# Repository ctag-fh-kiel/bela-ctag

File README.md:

## Resources regarding [CTAG-audio](http://ctag-audio.de/) capes for BeagleBone single board computers.

See [Wiki](https://github.com/ctag-fh-kiel/bela-ctag/wiki) for getting started with native Linux applications and CTAG multi-audio boards.

*CTAG multi-audio IO capes are compatible with the ultra-low-latency [Bela platform](http://bela.io/) and are available via [Bela's online shop](https://shop.bela.io/ctag).*

## Open source hardware resources include: 
- Schematic in pdf 
- Kicad 4.0.7 project data (PCB does not contain routed copper layers at this point --> will be added after some time together with BOM etc.)
- Licensed under [cc-by-nc-sa-4.0](https://creativecommons.org/licenses/by-nc-sa/4.0)

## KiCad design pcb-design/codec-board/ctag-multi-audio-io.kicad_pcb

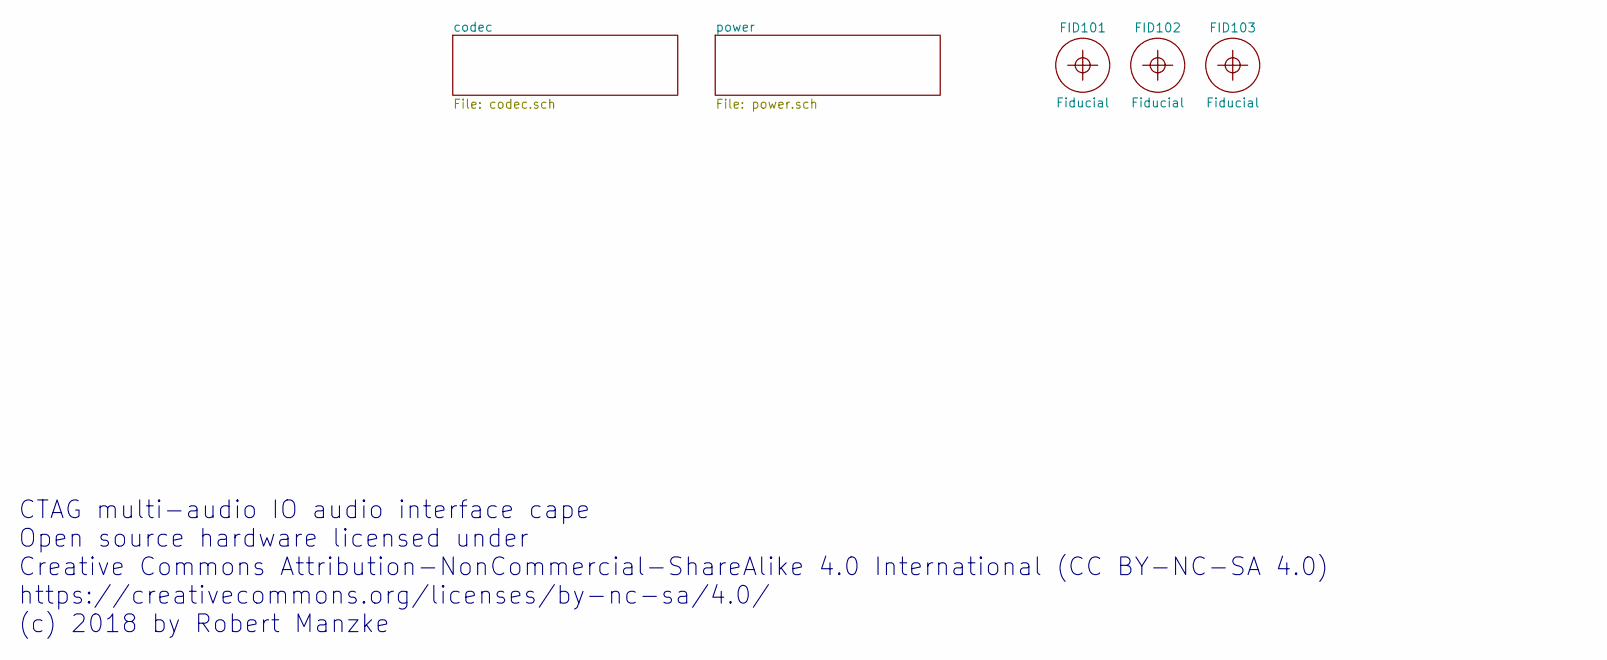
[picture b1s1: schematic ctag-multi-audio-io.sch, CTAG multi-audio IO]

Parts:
FID101, FID102, FID103: Fiducial; Fiducial_1mm_Dia_2.54mm_Outer_CopperTop

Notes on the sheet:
CTAG multi-audio IO audio interface cape Open source hardware licensed under Creative Commons Attribution-NonCommercial-ShareAlike 4.0 International (CC BY-NC-SA 4.0) https://creativecommons.org/licenses/by-nc-sa/4.0/ (c) 2018 by Robert Manzke

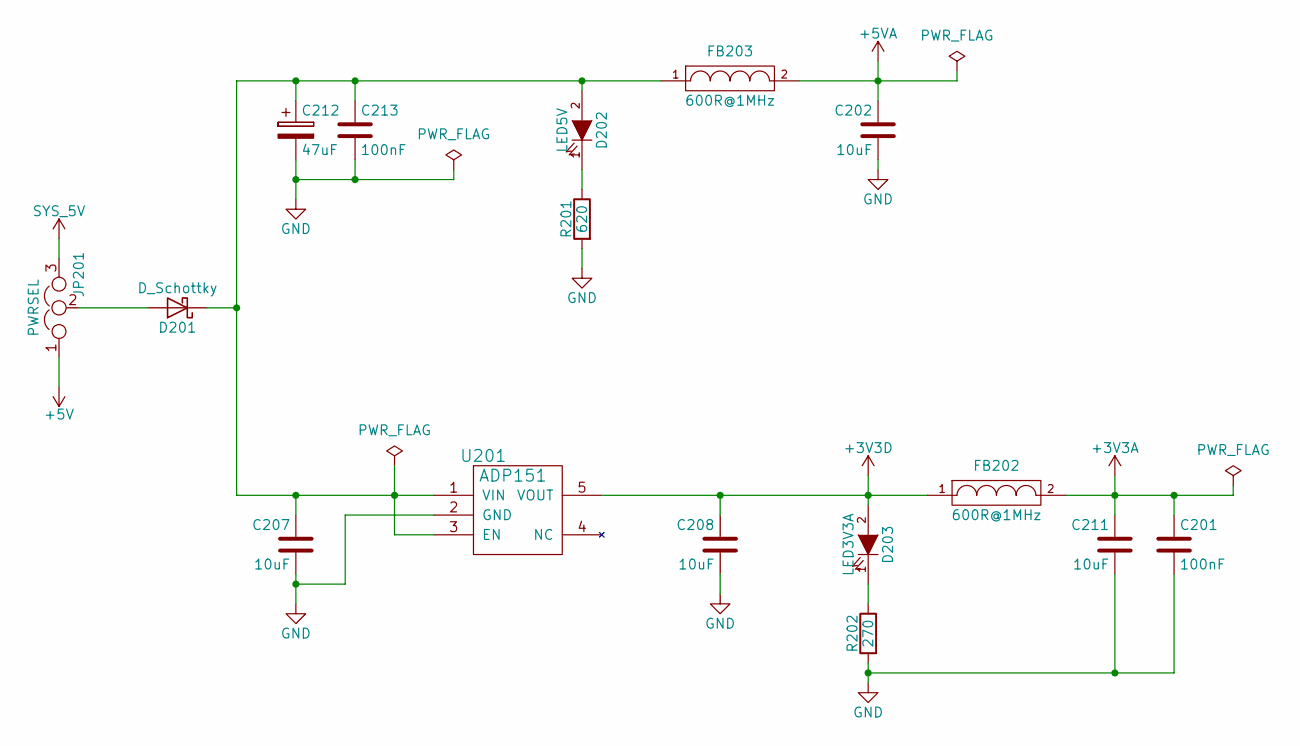
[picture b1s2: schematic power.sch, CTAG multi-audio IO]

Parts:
C201, C213: 100nF; C_0603
C202, C207, C208, C211: 10uF; C_0805
C212: 47uF; TantalC_SizeA_EIA-3216_Reflow
D201: D_Schottky; SOD-123
D202: LED5V; LED-0603
D203: LED3V3A; LED-0603
FB202, FB203: 600R@1MHz; C_0805
JP201: PWRSEL; Pin_Header_Straight_1x03
R201: 620; C_0603
R202: 270; C_0603
U201: ADP151; TSOT-23-5

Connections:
+3V3A: C201.1, C211.1, FB202.2; also elsewhere on the board
+3V3D: C208.1, D203.2 (A), FB202.1, U201.5 (VOUT); also elsewhere on the board
+5V: JP201.1; also elsewhere on the board
+5VA: C202.1, FB203.2; also elsewhere on the board
GND: C201.2, C202.2, C207.2, C208.2, C211.2, C212.2, C213.2, R201.2, R202.2, U201.2 (GND); also elsewhere on the board
unnamed: C207.1, C212.1, C213.1, D201.1 (K), D202.2 (A), FB203.1, U201.1 (VIN), U201.3 (EN)
unnamed: D201.2 (A), JP201.2
unnamed: D202.1 (K), R201.1
unnamed: D203.1 (K), R202.1
SYS_5V: JP201.3; also elsewhere on the board

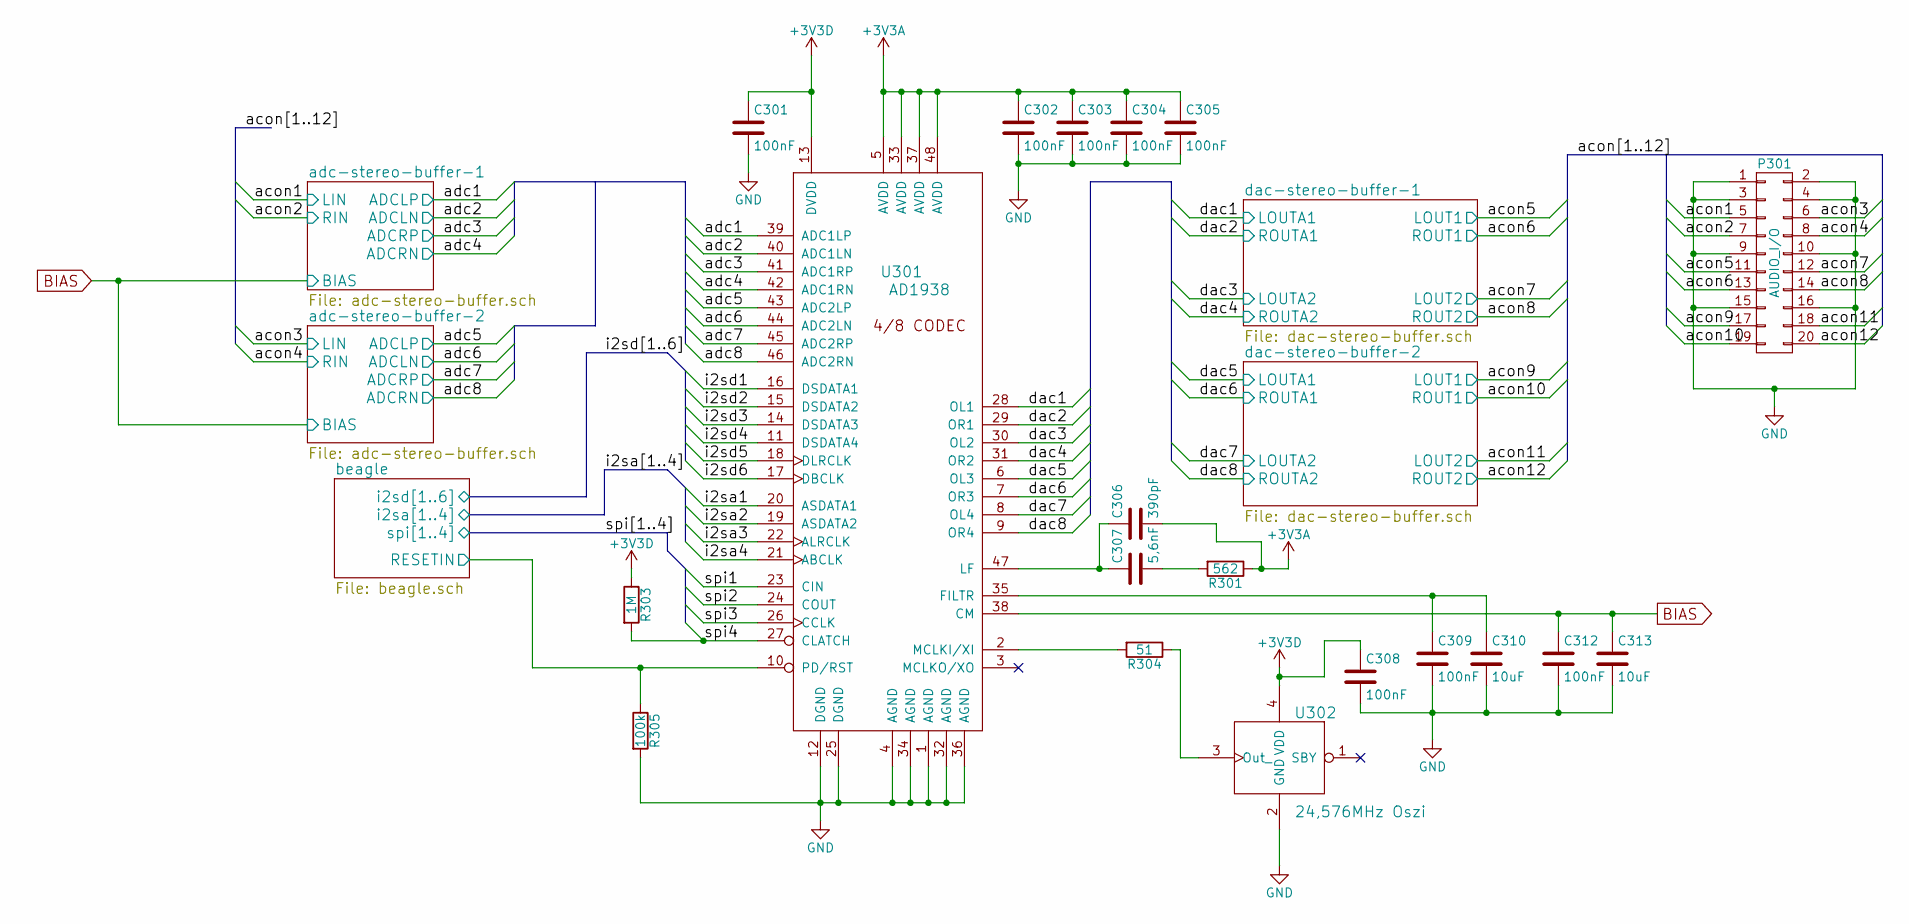
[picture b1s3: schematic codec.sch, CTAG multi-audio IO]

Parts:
C301, C302, C303, C304, C305, C308, C309, C312: 100nF; C_0603
C306: 390pF; C_0603
C307: 5,6nF; C_0603
C310, C313: 10uF; C_0805
P301: AUDIO_I/O; Pin_Header_Angled_2x10
R301: 562; C_0603
R303: 1M; C_0603
R304: 51; C_0603
R305: 100k; C_0603
U301: AD1938; LQFP-48_7x7mm_Pitch0.5mm
U302: 24,576MHz Oszi; Oszi_3.2x2.5mm

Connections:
+3V3A: C302.1, C303.1, C304.1, C305.1, C306.2, R301.1, U301.5 (AVDD), U301.33 (AVDD), U301.37 (AVDD), U301.48 (AVDD); also elsewhere on the board
+3V3D: C301.1, C308.1, R303.1, U301.13 (DVDD), U302.4 (VDD); also elsewhere on the board
/codec/acon1: P301.5; also elsewhere on the board
/codec/acon2: P301.7; also elsewhere on the board
/codec/acon3: P301.6; also elsewhere on the board
/codec/acon4: P301.8; also elsewhere on the board
/codec/acon5: P301.11; also elsewhere on the board
/codec/acon6: P301.13; also elsewhere on the board
/codec/acon7: P301.12; also elsewhere on the board
/codec/acon8: P301.14; also elsewhere on the board
/codec/acon9: P301.17; also elsewhere on the board
/codec/acon10: P301.19; also elsewhere on the board
/codec/acon11: P301.18; also elsewhere on the board
/codec/acon12: P301.20; also elsewhere on the board
/codec/adc1: U301.39 (ADC1LP); also elsewhere on the board
/codec/adc2: U301.40 (ADC1LN); also elsewhere on the board
/codec/adc3: U301.41 (ADC1RP); also elsewhere on the board
/codec/adc4: U301.42 (ADC1RN); also elsewhere on the board
/codec/adc5: U301.43 (ADC2LP); also elsewhere on the board
/codec/adc6: U301.44 (ADC2LN); also elsewhere on the board
/codec/adc7: U301.45 (ADC2RP); also elsewhere on the board
/codec/adc8: U301.46 (ADC2RN); also elsewhere on the board
/codec/beagle/RESETIN: R305.1, U301.10 (PD/RST); also elsewhere on the board
/codec/dac1: U301.28 (OL1); also elsewhere on the board
/codec/dac2: U301.29 (OR1); also elsewhere on the board
/codec/dac3: U301.30 (OL2); also elsewhere on the board
/codec/dac4: U301.31 (OR2); also elsewhere on the board
/codec/dac5: U301.6 (OL3); also elsewhere on the board
/codec/dac6: U301.7 (OR3); also elsewhere on the board
/codec/dac7: U301.8 (OL4); also elsewhere on the board
/codec/dac8: U301.9 (OR4); also elsewhere on the board
/codec/i2sa1: U301.20 (ASDATA1); also elsewhere on the board
/codec/i2sa2: U301.19 (ASDATA2); also elsewhere on the board
/codec/i2sa3: U301.22 (ALRCLK); also elsewhere on the board
/codec/i2sa4: U301.21 (ABCLK); also elsewhere on the board
/codec/i2sd1: U301.16 (DSDATA1); also elsewhere on the board
/codec/i2sd2: U301.15 (DSDATA2); also elsewhere on the board
/codec/i2sd3: U301.14 (DSDATA3)
/codec/i2sd4: U301.11 (DSDATA4)
/codec/i2sd5: U301.18 (DLRCLK); also elsewhere on the board
/codec/i2sd6: U301.17 (DBCLK); also elsewhere on the board
/codec/spi1: U301.23 (CIN); also elsewhere on the board
/codec/spi2: U301.24 (COUT); also elsewhere on the board
/codec/spi3: U301.26 (CCLK); also elsewhere on the board
/codec/spi4: R303.2, U301.27 (CLATCH); also elsewhere on the board
BIAS: C312.1, C313.1, U301.38 (CM); also elsewhere on the board
GND: C301.2, C302.2, C303.2, C304.2, C305.2, C308.2, C309.2, C310.2, C312.2, C313.2, P301.1, P301.2, P301.3, P301.4, P301.9, P301.10, P301.15, P301.16, R305.2, U301.1 (AGND), U301.4 (AGND), U301.12 (DGND), U301.25 (DGND), U301.32 (AGND), U301.34 (AGND), U301.36 (AGND), U302.2 (GND); also elsewhere on the board
unnamed: C306.1, C307.1, U301.47 (LF)
unnamed: C307.2, R301.2
unnamed: C309.1, C310.1, U301.35 (FILTR)
unnamed: R304.1, U302.3 (Out_)
unnamed: R304.2, U301.2 (MCLKI/XI)

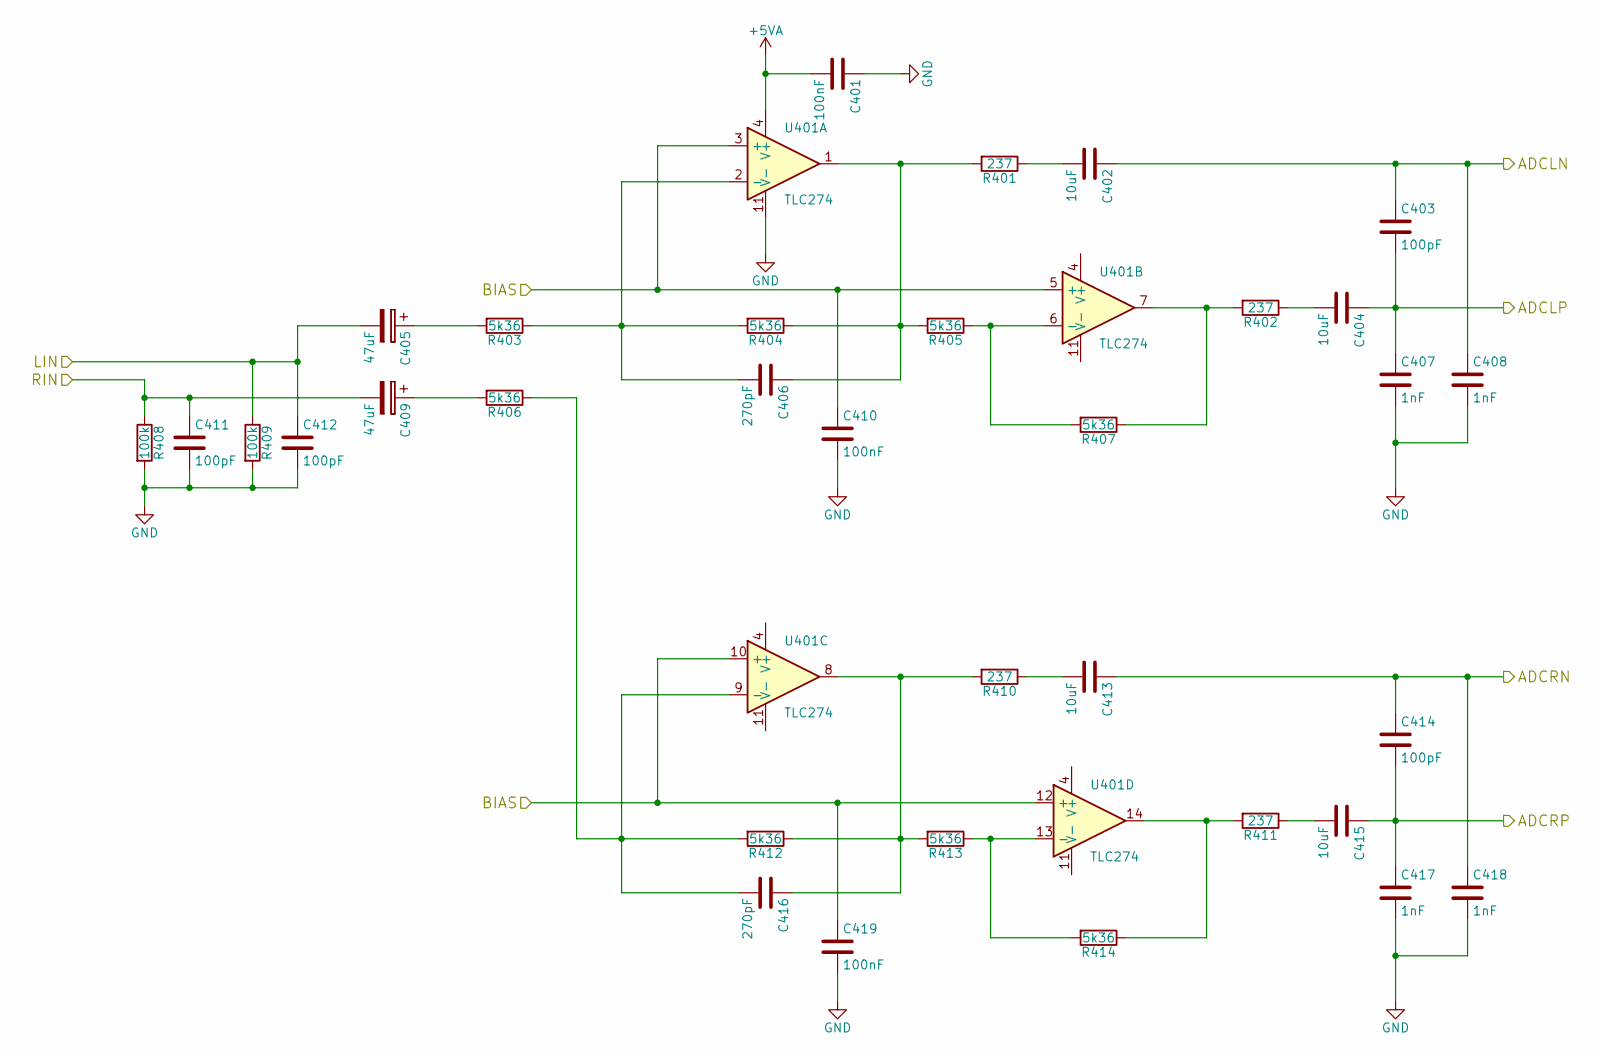
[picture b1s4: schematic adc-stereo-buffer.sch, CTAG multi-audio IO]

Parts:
C401, C410, C419: 100nF; C_0603
C402, C404, C413, C415: 10uF; C_0805
C403, C411, C412, C414: 100pF; C_0603
C405, C409: 47uF; TantalC_SizeA_EIA-3216_Reflow
C406, C416: 270pF; C_0603
C407, C408, C417, C418: 1nF; C_0603
R401, R402, R410, R411: 237; C_0603
R403, R404, R405, R406, R407, R412, R413, R414: 5k36; C_0603
R408, R409: 100k; C_0603
U401: TLC274; TSSOP-14_4.4x5mm_Pitch0.65mm

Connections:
+5VA: C401.2, U401.4 (V+); also elsewhere on the board
/codec/acon1: C405.2, C412.1, R409.1; also elsewhere on the board
/codec/acon2: C409.2, C411.1, R408.1; also elsewhere on the board
/codec/adc1: C403.2, C404.1, C407.1; also elsewhere on the board
/codec/adc2: C402.1, C403.1, C408.1; also elsewhere on the board
/codec/adc3: C414.2, C415.1, C417.1; also elsewhere on the board
/codec/adc4: C413.1, C414.1, C418.1; also elsewhere on the board
BIAS: C410.1, C419.1, U401.3 (+), U401.5 (+), U401.10 (+), U401.12 (+); also elsewhere on the board
GND: C401.1, C407.2, C408.2, C410.2, C411.2, C412.2, C417.2, C418.2, C419.2, R408.2, R409.2, U401.11 (V-); also elsewhere on the board
unnamed: C402.2, R401.1
unnamed: C404.2, R402.1
unnamed: C405.1, R403.2
unnamed: C406.1, R401.2, R404.1, R405.2, U401.1
unnamed: C406.2, R403.1, R404.2, U401.2 (-)
unnamed: C409.1, R406.2
unnamed: C413.2, R410.1
unnamed: C415.2, R411.1
unnamed: C416.1, R410.2, R412.1, R413.2, U401.8
unnamed: C416.2, R406.1, R412.2, U401.9 (-)
unnamed: R402.2, R407.1, U401.7
unnamed: R405.1, R407.2, U401.6 (-)
unnamed: R411.2, R414.1, U401.14
unnamed: R413.1, R414.2, U401.13 (-)

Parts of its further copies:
C501, C510, C519: 100nF; C_0603
C502, C504, C513, C515: 10uF; C_0805
C503, C511, C512, C514: 100pF; C_0603
C505, C509: 47uF; TantalC_SizeA_EIA-3216_Reflow
C506, C516: 270pF; C_0603
C507, C508, C517, C518: 1nF; C_0603
R501, R502, R510, R511: 237; C_0603
R503, R504, R505, R506, R507, R512, R513, R514: 5k36; C_0603
R508, R509: 100k; C_0603
U501: TLC274; TSSOP-14_4.4x5mm_Pitch0.65mm

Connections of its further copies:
+5VA: C501.2, U501.4 (V+); also elsewhere on the board
/codec/acon3: C505.2, C512.1, R509.1; also elsewhere on the board
/codec/acon4: C509.2, C511.1, R508.1; also elsewhere on the board
/codec/adc5: C503.2, C504.1, C507.1; also elsewhere on the board
/codec/adc6: C502.1, C503.1, C508.1; also elsewhere on the board
/codec/adc7: C514.2, C515.1, C517.1; also elsewhere on the board
/codec/adc8: C513.1, C514.1, C518.1; also elsewhere on the board
BIAS: C510.1, C519.1, U501.3 (+), U501.5 (+), U501.10 (+), U501.12 (+); also elsewhere on the board
GND: C501.1, C507.2, C508.2, C510.2, C511.2, C512.2, C517.2, C518.2, C519.2, R508.2, R509.2, U501.11 (V-); also elsewhere on the board
unnamed: C502.2, R501.1
unnamed: C504.2, R502.1
unnamed: C505.1, R503.2
unnamed: C506.1, R501.2, R504.1, R505.2, U501.1
unnamed: C506.2, R503.1, R504.2, U501.2 (-)
unnamed: C509.1, R506.2
unnamed: C513.2, R510.1
unnamed: C515.2, R511.1
unnamed: C516.1, R510.2, R512.1, R513.2, U501.8
unnamed: C516.2, R506.1, R512.2, U501.9 (-)
unnamed: R502.2, R507.1, U501.7
unnamed: R505.1, R507.2, U501.6 (-)
unnamed: R511.2, R514.1, U501.14
unnamed: R513.1, R514.2, U501.13 (-)

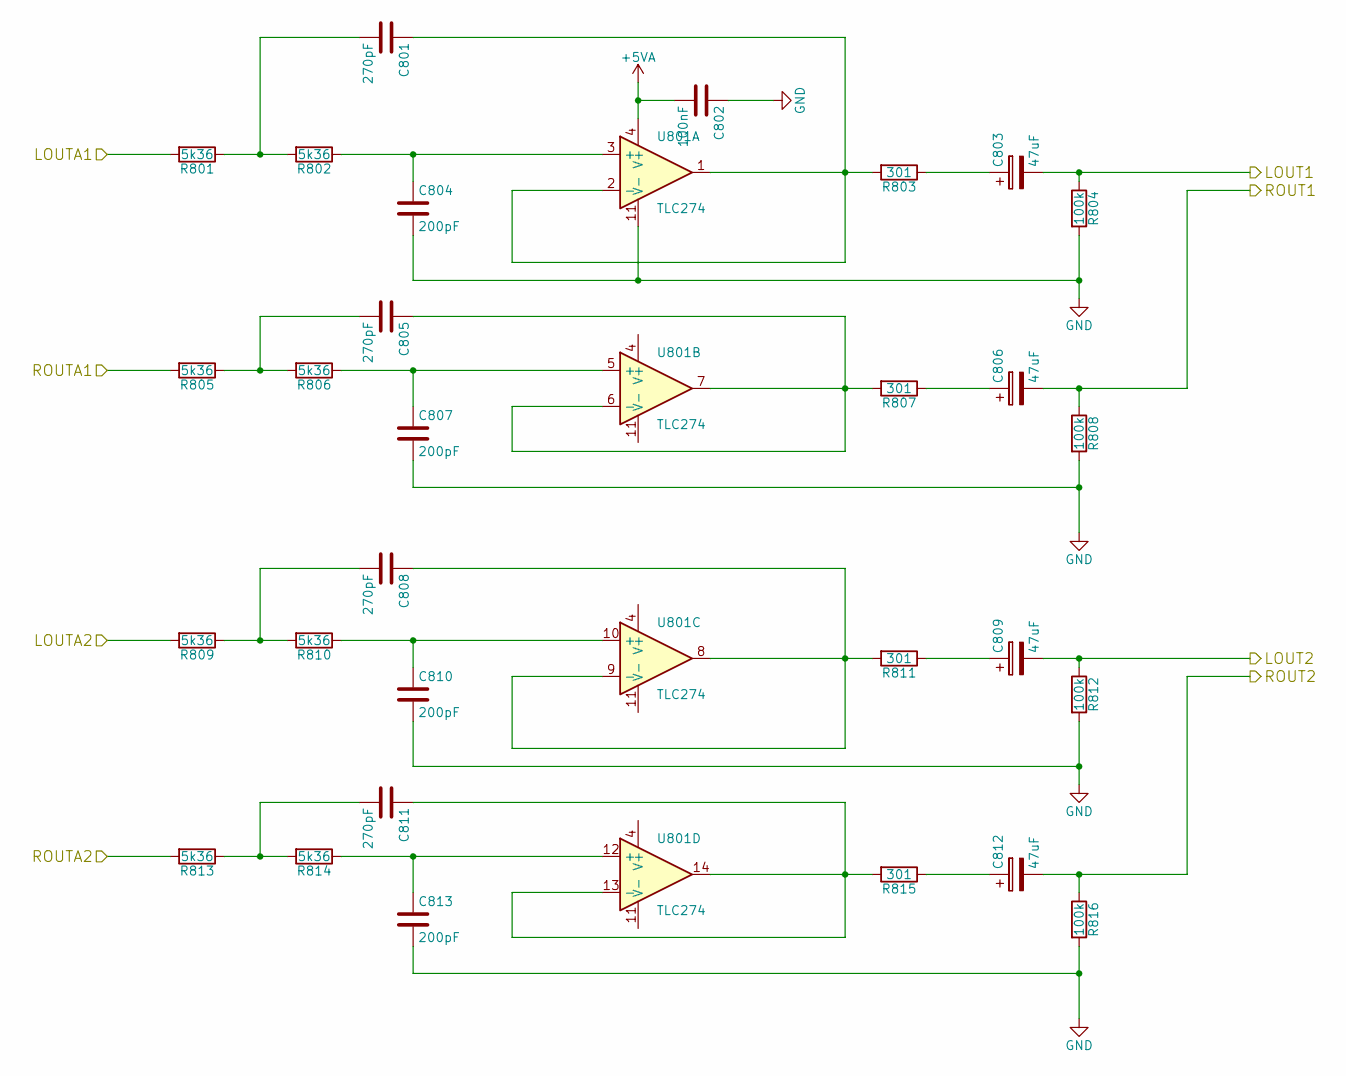
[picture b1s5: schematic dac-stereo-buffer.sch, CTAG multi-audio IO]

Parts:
C601, C605, C608, C611: 270pF; C_0603
C602: 100nF; C_0603
C603, C606, C609, C612: 47uF; TantalC_SizeA_EIA-3216_Reflow
C604, C607, C610, C613: 200pF; C_0603
R601, R602, R605, R606, R609, R610, R613, R614: 5k36; C_0603
R603, R607, R611, R615: 301; C_0603
R604, R608, R612, R616: 100k; C_0603
U601: TLC274; TSSOP-14_4.4x5mm_Pitch0.65mm

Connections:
+5VA: C602.2, U601.4 (V+); also elsewhere on the board
/codec/acon5: C603.2, R604.1; also elsewhere on the board
/codec/acon6: C606.2, R608.1; also elsewhere on the board
/codec/acon7: C609.2, R612.1; also elsewhere on the board
/codec/acon8: C612.2, R616.1; also elsewhere on the board
/codec/dac1: R601.2; also elsewhere on the board
/codec/dac2: R605.2; also elsewhere on the board
/codec/dac3: R609.2; also elsewhere on the board
/codec/dac4: R613.2; also elsewhere on the board
GND: C602.1, C604.2, C607.2, C610.2, C613.2, R604.2, R608.2, R612.2, R616.2, U601.11 (V-); also elsewhere on the board
unnamed: C601.1, R603.2, U601.1, U601.2 (-)
unnamed: C601.2, R601.1, R602.2
unnamed: C603.1, R603.1
unnamed: C604.1, R602.1, U601.3 (+)
unnamed: C605.1, R607.2, U601.6 (-), U601.7
unnamed: C605.2, R605.1, R606.2
unnamed: C606.1, R607.1
unnamed: C607.1, R606.1, U601.5 (+)
unnamed: C608.1, R611.2, U601.8, U601.9 (-)
unnamed: C608.2, R609.1, R610.2
unnamed: C609.1, R611.1
unnamed: C610.1, R610.1, U601.10 (+)
unnamed: C611.1, R615.2, U601.13 (-), U601.14
unnamed: C611.2, R613.1, R614.2
unnamed: C612.1, R615.1
unnamed: C613.1, R614.1, U601.12 (+)

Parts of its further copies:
C801, C805, C808, C811: 270pF; C_0603
C802: 100nF; C_0603
C803, C806, C809, C812: 47uF; TantalC_SizeA_EIA-3216_Reflow
C804, C807, C810, C813: 200pF; C_0603
R801, R802, R805, R806, R809, R810, R813, R814: 5k36; C_0603
R803, R807, R811, R815: 301; C_0603
R804, R808, R812, R816: 100k; C_0603
U801: TLC274; TSSOP-14_4.4x5mm_Pitch0.65mm

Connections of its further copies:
+5VA: C802.2, U801.4 (V+); also elsewhere on the board
/codec/acon9: C803.2, R804.1; also elsewhere on the board
/codec/acon10: C806.2, R808.1; also elsewhere on the board
/codec/acon11: C809.2, R812.1; also elsewhere on the board
/codec/acon12: C812.2, R816.1; also elsewhere on the board
/codec/dac5: R801.2; also elsewhere on the board
/codec/dac6: R805.2; also elsewhere on the board
/codec/dac7: R809.2; also elsewhere on the board
/codec/dac8: R813.2; also elsewhere on the board
GND: C802.1, C804.2, C807.2, C810.2, C813.2, R804.2, R808.2, R812.2, R816.2, U801.11 (V-); also elsewhere on the board
unnamed: C801.1, R803.2, U801.1, U801.2 (-)
unnamed: C801.2, R801.1, R802.2
unnamed: C803.1, R803.1
unnamed: C804.1, R802.1, U801.3 (+)
unnamed: C805.1, R807.2, U801.6 (-), U801.7
unnamed: C805.2, R805.1, R806.2
unnamed: C806.1, R807.1
unnamed: C807.1, R806.1, U801.5 (+)
unnamed: C808.1, R811.2, U801.8, U801.9 (-)
unnamed: C808.2, R809.1, R810.2
unnamed: C809.1, R811.1
unnamed: C810.1, R810.1, U801.10 (+)
unnamed: C811.1, R815.2, U801.13 (-), U801.14
unnamed: C811.2, R813.1, R814.2
unnamed: C812.1, R815.1
unnamed: C813.1, R814.1, U801.12 (+)

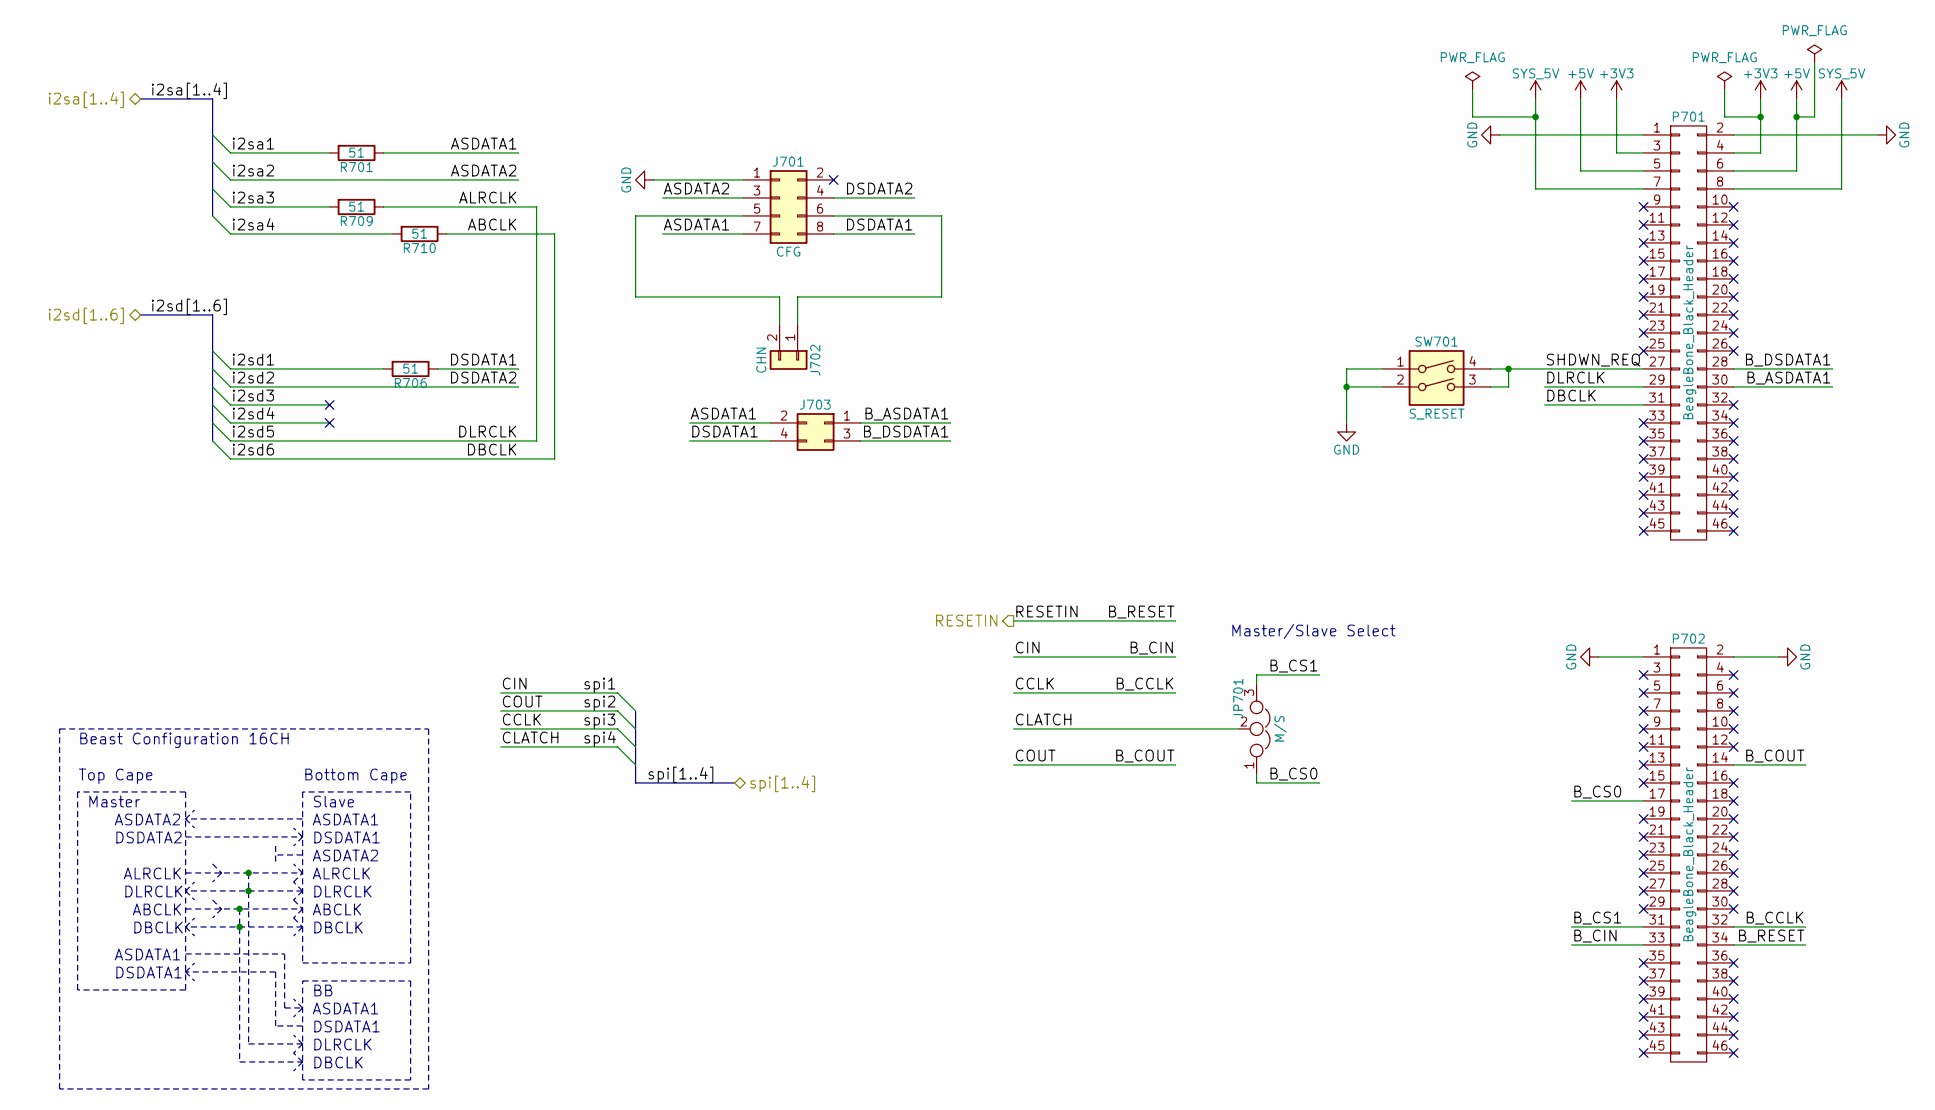
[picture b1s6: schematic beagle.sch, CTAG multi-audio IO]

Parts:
J701: CFG; Pin_Header_Straight_2x04
J702: CHN; Pin_Header_Straight_1x02
J703: Pin_Header_Straight_1x04
JP701: M/S; Pin_Header_Straight_1x03
P701, P702: BeagleBone_Black_Header; Pin_Header_Straight_2x23
R701, R706, R709, R710: 51; C_0603
SW701: S_RESET; PTS810

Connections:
+3V3: P701.3, P701.4
+5V: P701.5, P701.6; also elsewhere on the board
/codec/beagle/ASDATA1: J701.7, J703.2, R701.1
/codec/beagle/B_ASDATA1: J703.1, P701.30
/codec/beagle/B_CS0: JP701.1, P702.17
/codec/beagle/B_CS1: JP701.3, P702.31
/codec/beagle/B_DSDATA1: J703.3, P701.28
/codec/beagle/DSDATA1: J701.8, J703.4, R706.1
/codec/beagle/RESETIN: P702.34; also elsewhere on the board
/codec/beagle/SHDWN_REQ: P701.27, SW701.3, SW701.4
/codec/i2sa1: R701.2; also elsewhere on the board
/codec/i2sa2: J701.3; also elsewhere on the board
/codec/i2sa3: R709.2; also elsewhere on the board
/codec/i2sa4: R710.2; also elsewhere on the board
/codec/i2sd1: R706.2; also elsewhere on the board
/codec/i2sd2: J701.4; also elsewhere on the board
/codec/i2sd5: P701.29, R709.1; also elsewhere on the board
/codec/i2sd6: P701.31, R710.1; also elsewhere on the board
/codec/spi1: P702.33; also elsewhere on the board
/codec/spi2: P702.14; also elsewhere on the board
/codec/spi3: P702.32; also elsewhere on the board
/codec/spi4: JP701.2; also elsewhere on the board
GND: J701.1, P701.1, P701.2, P702.1, P702.2, SW701.1, SW701.2; also elsewhere on the board
unnamed: J701.5, J702.2
unnamed: J701.6, J702.1
SYS_5V: P701.7, P701.8; also elsewhere on the board

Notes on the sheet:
Master/Slave Select
Master
Slave
ASDATA2
ASDATA1
DSDATA2
DSDATA1
ALRCLK
DLRCLK
ABCLK
DBCLK
Beast Configuration 16CH
Bottom Cape
Top Cape

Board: 4 copper layers, 177 parts (0 on the bottom side), 127 nets, no tracks yet.

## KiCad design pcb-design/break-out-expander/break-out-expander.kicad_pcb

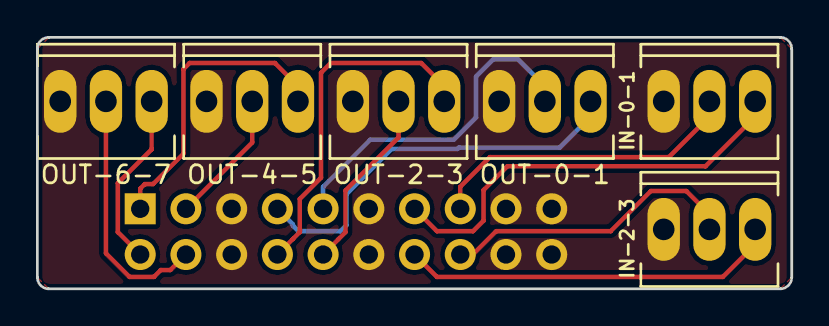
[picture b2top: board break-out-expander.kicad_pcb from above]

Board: 2 copper layers, 41.9 x 14.0 mm, 7 parts (1 on the bottom side), 13 nets.

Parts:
I/O: Pin_Header_Straight_2x10
IN-0-1, IN-2-3: Socket_MOLEX-KK-RM2-54mm_Lock_3pin_straight
OUT-0-1, OUT-2-3, OUT-4-5, OUT-6-7: Socket_MOLEX-KK-RM2-54mm_Lock_3pin_straight

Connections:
GND: I/O.5, I/O.6, I/O.11, I/O.12, I/O.17, I/O.18, I/O.19, I/O.20, IN-0-1.1, IN-2-3.1, OUT-0-1.1, OUT-2-3.1, OUT-4-5.1, OUT-6-7.1
unnamed: I/O.15, IN-0-1.2
unnamed: I/O.13, IN-0-1.3
unnamed: I/O.16, IN-2-3.2
unnamed: I/O.14, IN-2-3.3
unnamed: I/O.9, OUT-0-1.2
unnamed: I/O.7, OUT-0-1.3
unnamed: I/O.10, OUT-2-3.2
unnamed: I/O.8, OUT-2-3.3
unnamed: I/O.3, OUT-4-5.2
unnamed: I/O.1, OUT-4-5.3
unnamed: I/O.4, OUT-6-7.2
unnamed: I/O.2, OUT-6-7.3

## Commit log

2018-10-28 initial public version

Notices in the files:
pcb-design/codec-board/ctag-multi-audio-io.kicad_pcb:
(c) 2016 by Robert Manzke
CTAG Cape 2|4  is licensed under
TBD
